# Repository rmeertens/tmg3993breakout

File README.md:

# tmg3993breakout
A PCB for the TMG 3993 sensor. Made in KICAD.

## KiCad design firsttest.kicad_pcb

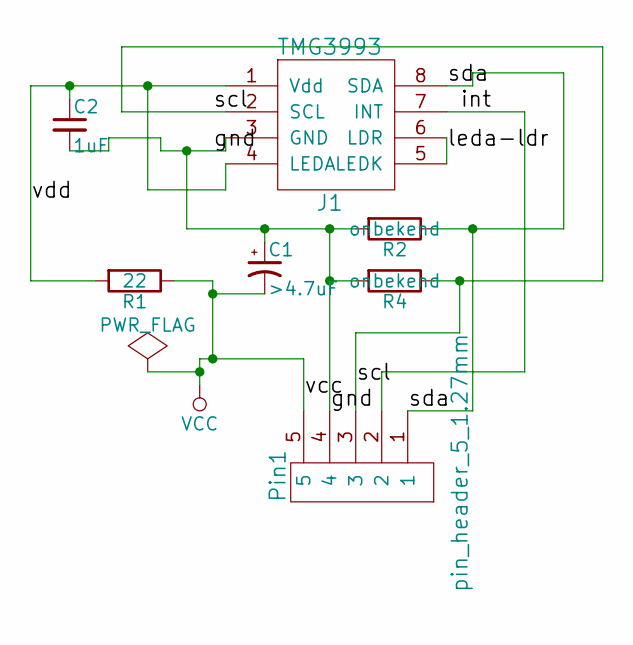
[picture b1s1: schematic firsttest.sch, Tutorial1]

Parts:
C1: >4.7uF; C_0805
C2: 1uF; C_0402
J1: TMG3993; TMG3993x
Pin1: pin_header_5_1.27mm; pinheader_5_1.27mm
R1: 22; R_0402
R2, R4: onbekend; R_0402

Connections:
/gnd: C1.1, C2.2, J1.3 (GND), Pin1.4, R2.2, R4.2
/int: J1.7 (INT), Pin1.2
/leda-ldr: J1.5 (LEDK), J1.6 (LDR)
/scl: J1.2 (SCL), Pin1.3, R4.1
/sda: J1.8 (SDA), Pin1.1, R2.1
/vdd: C2.1, J1.1 (Vdd), J1.4 (LEDA), R1.2
VCC: C1.2, Pin1.5, R1.1

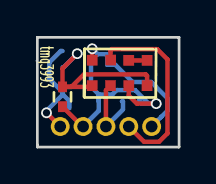
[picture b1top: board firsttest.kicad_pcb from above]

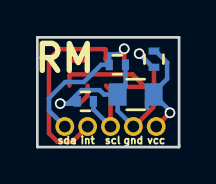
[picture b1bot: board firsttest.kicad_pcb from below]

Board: 2 copper layers, 7.9 x 6.1 mm, 7 parts (4 on the bottom side), 7 nets.

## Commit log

2016-02-24 added everything
